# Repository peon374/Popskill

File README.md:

# Popskill

Pentesting security platform

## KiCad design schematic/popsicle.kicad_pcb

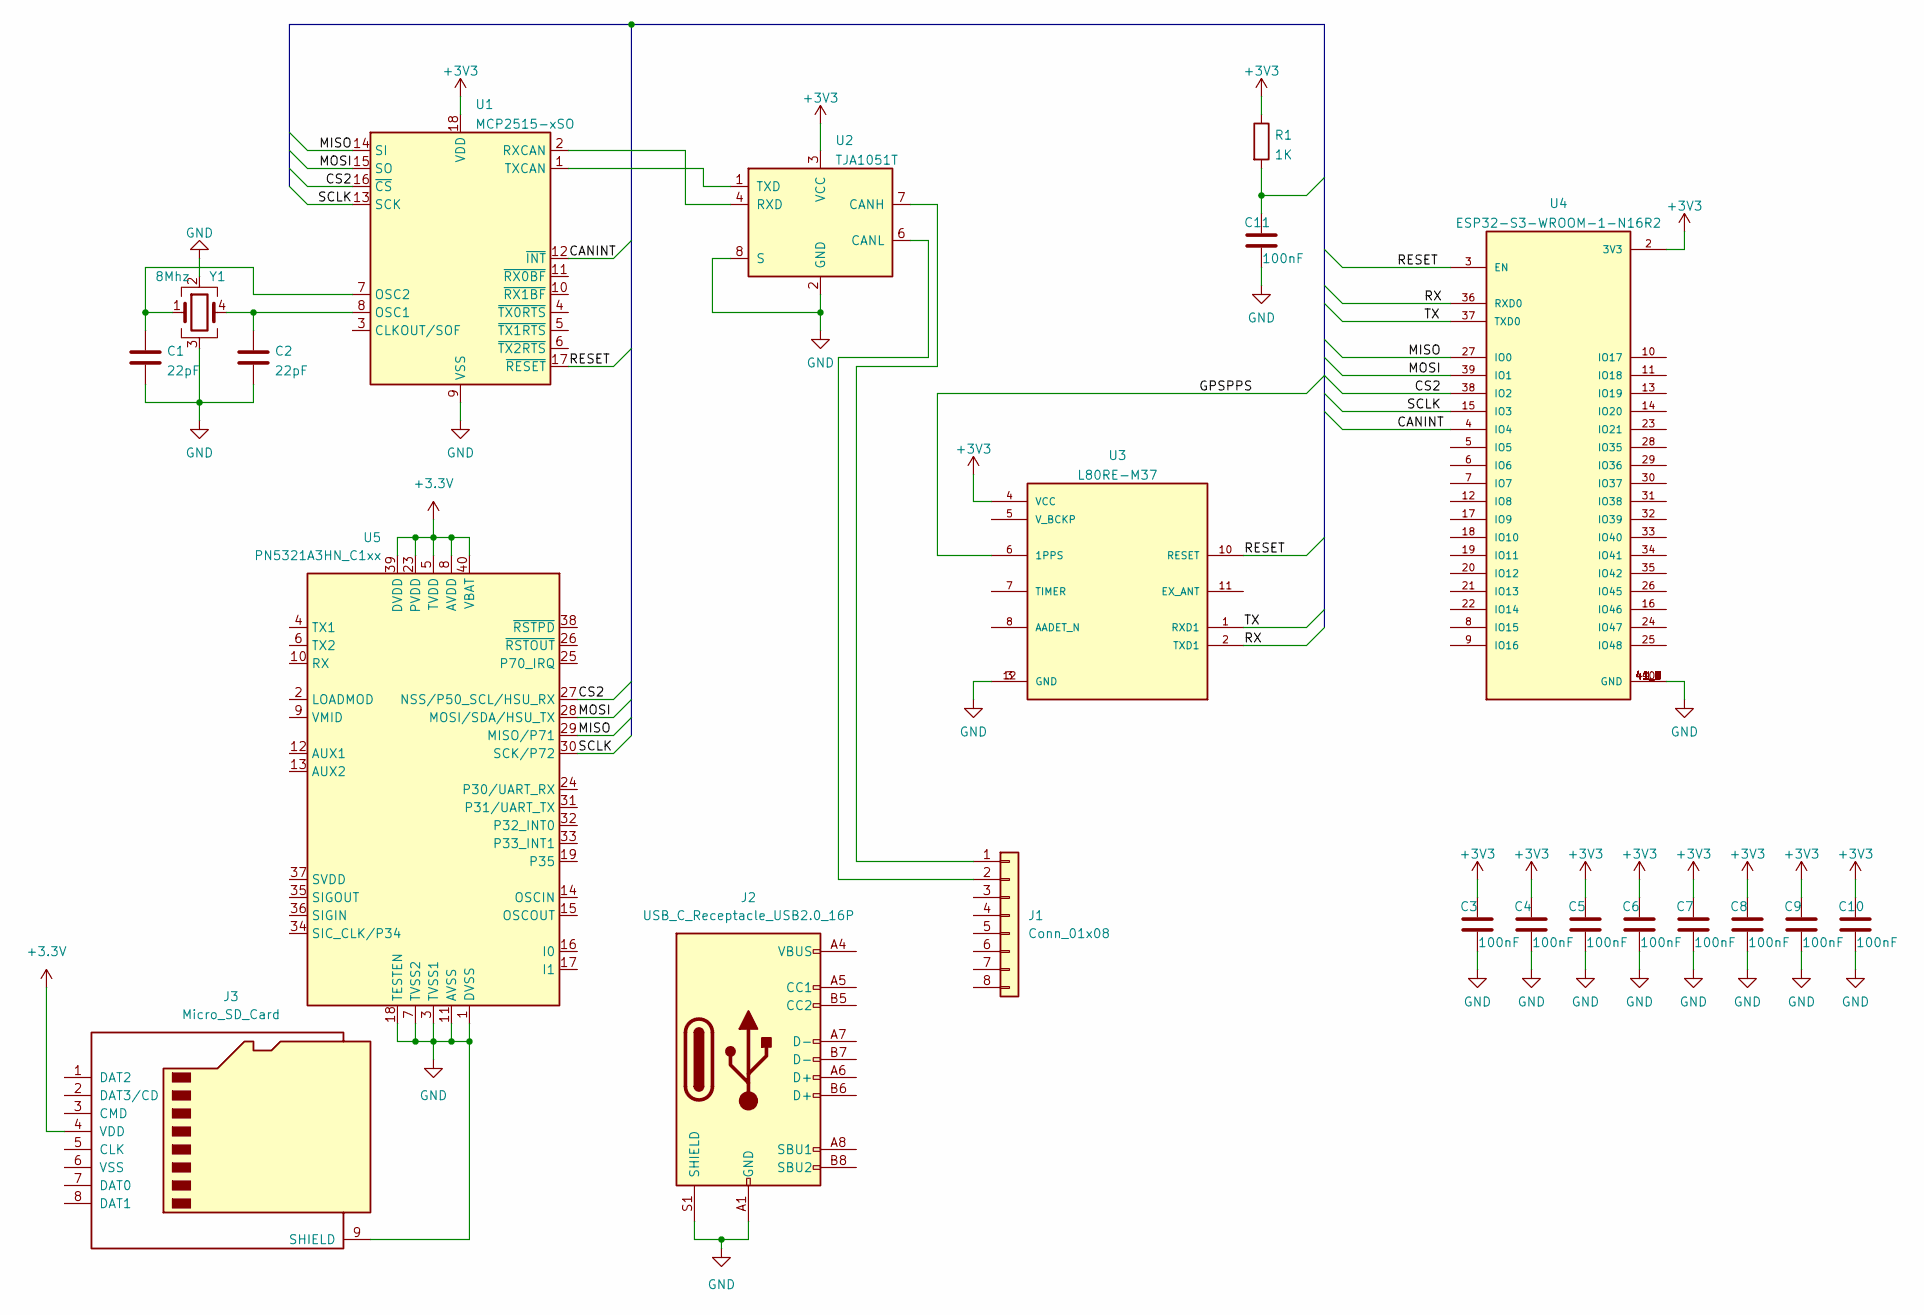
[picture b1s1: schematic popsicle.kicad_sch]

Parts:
C1, C2: 22pF; C_0402_1005Metric
C3, C4, C5, C6, C7, C8, C9, C10, C11: 100nF; C_0402_1005Metric; LCSC C1525
J1: Conn_01x08; maglock-8pin
J2: USB_C_Receptacle_USB2.0_16P; USB_C_Receptacle_GCT_USB4105-xx-A_16P_TopMnt_Horizontal
J3: Micro_SD_Card; microSD_HC_Molex_104031-0811
R1: 1K; R_0402_1005Metric; LCSC C11702
U1: MCP2515-xSO; QFN-20-1EP_4x4mm_P0.5mm_EP2.5x2.5mm; LCSC C637693
U2: TJA1051T; SOIC-8_3.9x4.9mm_P1.27mm
U3: L80RE-M37; XCVR_L80RE-M37; LCSC C3029061
U4: ESP32-S3-WROOM-1-N16R2; XCVR_ESP32-S3-WROOM-1-N16R2; PARTREV v1.0
U5: PN5321A3HN_C1xx; HVQFN-40-1EP_6x6mm_P0.5mm_EP4.1x4.1mm
Y1: 8Mhz; Crystal_SMD_2016-4Pin_2.0x1.6mm

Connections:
+3.3V: J3.4 (VDD), U5.5 (TVDD), U5.8 (AVDD), U5.23 (PVDD), U5.39 (DVDD), U5.40 (VBAT)
+3V3: C3.1, C4.1, C5.1, C6.1, C7.1, C8.1, C9.1, C10.1, R1.1, U1.18 (VDD), U2.3 (VCC), U3.4 (VCC), U4.2 (3V3)
/CANINT: U1.12 (~INT), U4.4 (IO4)
/CS2: U1.16 (~CS), U4.38 (IO2), U5.27 (NSS/P50_SCL/HSU_RX)
/GPSPPS: U3.6 (1PPS)
/MISO: U1.14 (SI), U4.27 (IO0), U5.29 (MISO/P71)
/MOSI: U1.15 (SO), U4.39 (IO1), U5.28 (MOSI/SDA/HSU_TX)
/RESET: U1.17 (~RESET), U3.10 (RESET), U4.3 (EN)
/RX: U3.2 (TXD1), U4.36 (RXD0)
/SCLK: U1.13 (SCK), U4.15 (IO3), U5.30 (SCK/P72)
/TX: U3.1 (RXD1), U4.37 (TXD0)
GND: C1.2, C2.2, C3.2, C4.2, C5.2, C6.2, C7.2, C8.2, C9.2, C10.2, C11.2, J2.A1 (GND), J2.A12 (GND), J2.B1 (GND), J2.B12 (GND), J2.S1 (SHIELD), J3.9 (SHIELD), U1.9 (VSS), U2.2 (GND), U2.8 (S), U3.3 (GND), U3.12 (GND), U4.1 (GND), U4.40 (GND), U4.41_1 (GND), U4.41_2 (GND), U4.41_3 (GND), U4.41_4 (GND), U4.41_5 (GND), U4.41_6 (GND), U4.41_7 (GND), U4.41_8 (GND), U4.41_9 (GND), U5.1 (DVSS), U5.3 (TVSS1), U5.7 (TVSS2), U5.11 (AVSS), U5.18 (TESTEN), U5.41 (AVSS), Y1.2, Y1.3
unnamed: C11.1, R1.2
unnamed: J1.1, U2.7 (CANH)
unnamed: J1.2, U2.6 (CANL)
unnamed: J2.A4 (VBUS), J2.A9 (VBUS), J2.B4 (VBUS), J2.B9 (VBUS)
unnamed: C2.1, U1.8 (OSC1), Y1.4
unnamed: C1.1, U1.7 (OSC2), Y1.1
unnamed: U1.2 (RXCAN), U2.4 (RXD)
unnamed: U1.1 (TXCAN), U2.1 (TXD)

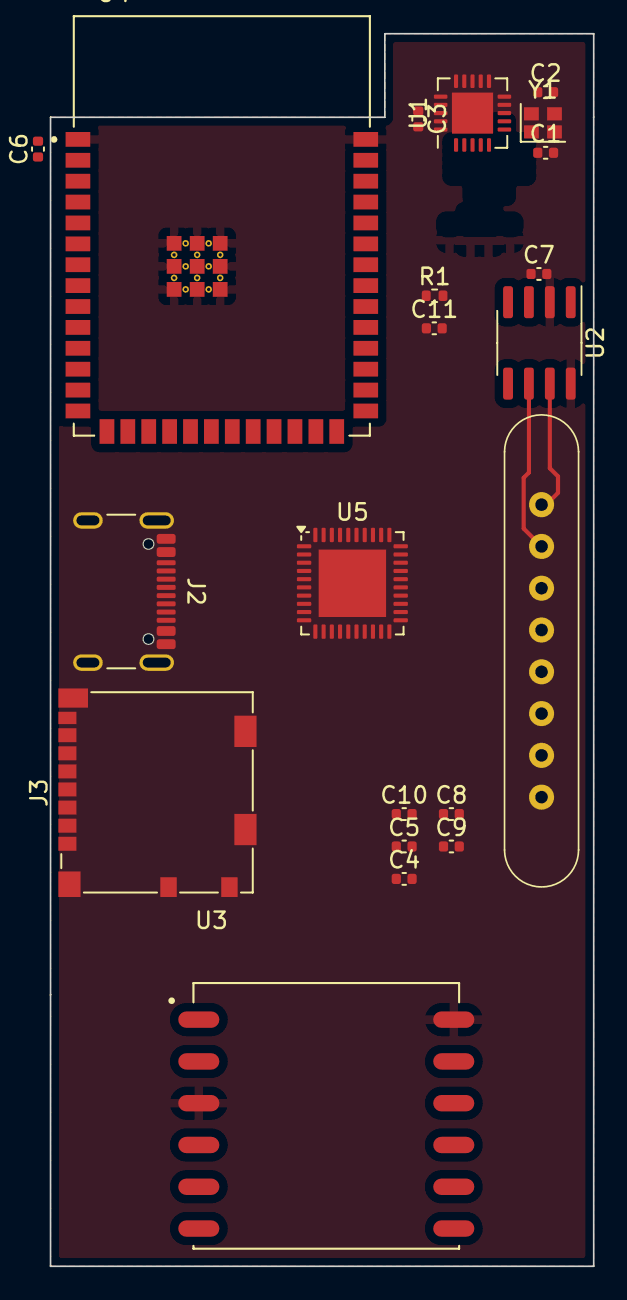
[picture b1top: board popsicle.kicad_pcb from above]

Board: 2 copper layers, 33.0 x 74.9 mm, 21 parts (0 on the bottom side), 19 nets.

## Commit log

2024-03-31 Initial add
2024-03-31 Removed backups
